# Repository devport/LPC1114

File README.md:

# LPC1114
LPC1114 in FreePascal

UNITS FOR:
--- ENC28J60, SH1106 OLED, OneWire, DS18B20, UART, SPI, ADC, SysTick Timer, Delay (Timers) and utility ---

Binutils:
Download http://ftp.gnu.org/gnu/binutils/binutils-2.20.tar.bz2
Unzip in binutils-2.20
Create a directory binutils-arm
From binutils-arm run: ../binutils-2.20/configure --target=arm-elf --disable-nls --prefix=directory_where_you_want_binutils_installed
Build using: make all install

or download binary for windows and copy to 'c:\cross':
https://svn.freepascal.org/svn/fpcbuild/binaries/i386-win32/

FPC:
1. Requires trunk version of FPC instal to 'c:\fpc'
2. Get source FPC -> extract to 'c:\fpc_src'
3. Copy lpc11xx.pp to fpc_src\rtl\embedded\arm and replace (my version is for LPC1114XL (2xSPI etc))
4. Go to fpc_src directory and Build using: 

PATH=C:\fpc\3.0.4\bin\i386-win32;C:\cross

make clean buildbase installbase CROSSINSTALL=1 OS_TARGET=embedded CPU_TARGET=arm SUBARCH=armv6m

* C:\fpc\3.0.4\bin\i386-win32 << directory FPC
* C:\cross  << binary files fpcBuild (arm-embedded-as, arm-embedded-ld, etc.)

5. Copy fpc_src\compiler\ppcrossarm.exe to fpc\3.0.4\bin\i386-win32
6. Copy directory fpc_src\rtl\units\arm-embedded to fpc\3.0.4\units

Compile projects using:

ppcrossarm  -Fu..\units -Sc -O1 -Cparmv6m -Parm -Tembedded -Wplpc1114FBD48_303 project.pas

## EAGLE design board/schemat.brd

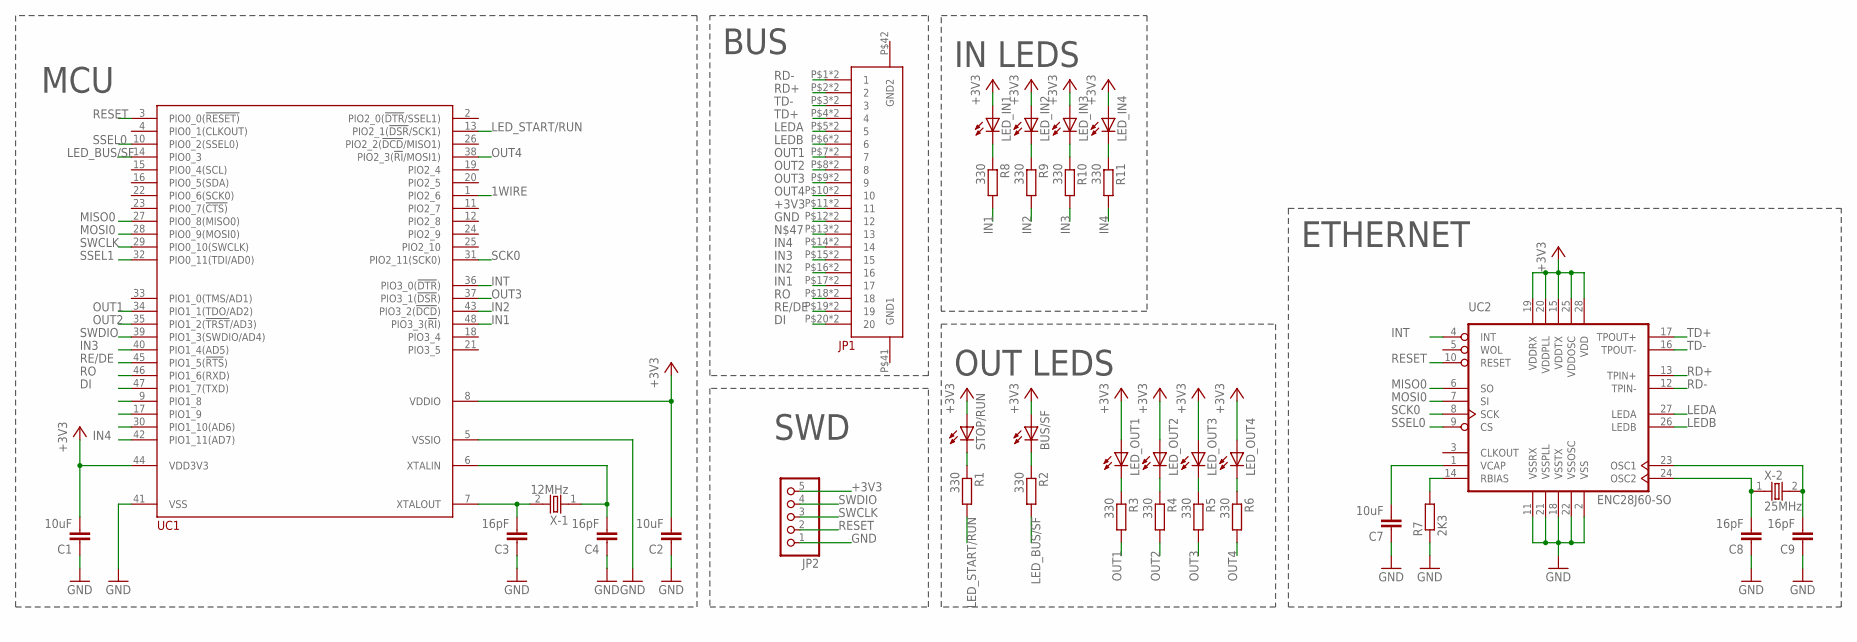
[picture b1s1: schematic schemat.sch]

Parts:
BUS/SF: LED3MM
C1, C2, C7: 10uF; C0805
C3, C4, C8, C9: 16pF; C0805
JP1: FFC(FPC)_ZIF_20_PINV; PCA-2C-20-V-3
JP2: PINHD-1X5; 1X05
LED_IN1, LED_IN2, LED_IN3, LED_IN4: LED3MM
LED_OUT1, LED_OUT2, LED_OUT3, LED_OUT4: LED3MM
R1, R2, R3, R4, R5, R6, R8, R9, R10, R11: 330; R0805W
R7: 2K3; R0805
STOP/RUN: LED3MM
UC1: NXP-LPC111X; LQFP48
UC2: ENC28J60-SO; SO28W
X-1: 12MHz; HC49UP
X-2: 25MHz; HC49UP

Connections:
1WIRE: UC1.1 (PIO2_6)
+3V3: BUS/SF.A, C1.2, C2.2, JP1.P$11 (11), JP1.P$31 (11), JP2.5, LED_IN1.A, LED_IN2.A, LED_IN3.A, LED_IN4.A, LED_OUT1.A, LED_OUT2.A, LED_OUT3.A, LED_OUT4.A, STOP/RUN.A, UC1.8 (VDDIO), UC1.44 (VDD3V3), UC2.15 (VDDTX), UC2.19 (VDDRX), UC2.20 (VDDPLL), UC2.25 (VDDOSC), UC2.28 (VDD)
DI: JP1.P$20 (20), JP1.P$40 (20), UC1.47 (PIO1_7(TXD))
GND: C1.1, C2.1, C3.1, C4.1, C7.1, C8.1, C9.1, JP1.P$12 (12), JP1.P$32 (12), JP2.1, R7.1, UC1.5 (VSSIO), UC1.41 (VSS), UC2.2 (VSS), UC2.11 (VSSRX), UC2.18 (VSSTX), UC2.21 (VSSPLL), UC2.22 (VSSOSC)
IN1: JP1.P$17 (17), JP1.P$37 (17), R8.2, UC1.48 (PIO3_3(!RI!))
IN2: JP1.P$16 (16), JP1.P$36 (16), R9.2, UC1.43 (PIO3_2(!DCD!))
IN3: JP1.P$15 (15), JP1.P$35 (15), R10.2, UC1.40 (PIO1_4(AD5))
IN4: JP1.P$14 (14), JP1.P$34 (14), R11.2, UC1.42 (PIO1_11(AD7))
INT: UC1.36 (PIO3_0(!DTR!)), UC2.4 (INT)
LEDA: JP1.P$5 (5), JP1.P$25 (5), UC2.27 (LEDA)
LEDB: JP1.P$6 (6), JP1.P$26 (6), UC2.26 (LEDB)
LED_BUS/SF: R2.2, UC1.14 (PIO0_3)
LED_START/RUN: R1.2, UC1.13 (PIO2_1(!DSR!/SCK1))
MISO0: UC1.27 (PIO0_8(MISO0)), UC2.6 (SO)
MOSI0: UC1.28 (PIO0_9(MOSI0)), UC2.7 (SI)
unnamed: C3.2, UC1.7 (XTALOUT), X-1.2
unnamed: C4.2, UC1.6 (XTALIN), X-1.1
unnamed: C8.2, UC2.24 (OSC2), X-2.1
unnamed: R1.1, STOP/RUN.K (C)
unnamed: LED_IN4.K (C), R11.1
unnamed: BUS/SF.K (C), R2.1
unnamed: LED_OUT4.K (C), R6.1
unnamed: LED_IN1.K (C), R8.1
unnamed: LED_IN2.K (C), R9.1
unnamed: LED_IN3.K (C), R10.1
unnamed: LED_OUT3.K (C), R5.1
unnamed: LED_OUT2.K (C), R4.1
unnamed: LED_OUT1.K (C), R3.1
unnamed: C9.2, UC2.23 (OSC1), X-2.2
unnamed: C7.2, UC2.1 (VCAP)
unnamed: R7.2, UC2.14 (RBIAS)
unnamed: JP1.P$13 (13), JP1.P$33 (13)
OUT1: JP1.P$7 (7), JP1.P$27 (7), R3.2, UC1.34 (PIO1_1(TDO/AD2))
OUT2: JP1.P$8 (8), JP1.P$28 (8), R4.2, UC1.35 (PIO1_2(!TRST!/AD3))
OUT3: JP1.P$9 (9), JP1.P$29 (9), R5.2, UC1.37 (PIO3_1(!DSR!))
OUT4: JP1.P$10 (10), JP1.P$30 (10), R6.2, UC1.38 (PIO2_3(!RI!/MOSI1))
RD+: JP1.P$2 (2), JP1.P$22 (2), UC2.13 (TPIN+)
RD-: JP1.P$1 (1), JP1.P$21 (1), UC2.12 (TPIN-)
RE/DE: JP1.P$19 (19), JP1.P$39 (19), UC1.45 (PIO1_5(!RTS!))
RESET: JP2.2, UC1.3 (PIO0_0(!RESET)), UC2.10 (RESET)
RO: JP1.P$18 (18), JP1.P$38 (18), UC1.46 (PIO1_6(RXD))
SCK0: UC1.31 (PIO2_11(SCK0)), UC2.8 (SCK)
SSEL0: UC1.10 (PIO0_2(SSEL0)), UC2.9 (CS)
SSEL1: UC1.32 (PIO0_11(TDI/AD0))
SWCLK: JP2.3, UC1.29 (PIO0_10(SWCLK))
SWDIO: JP2.4, UC1.39 (PIO1_3(SWDIO/AD4))
TD+: JP1.P$4 (4), JP1.P$24 (4), UC2.17 (TPOUT+)
TD-: JP1.P$3 (3), JP1.P$23 (3), UC2.16 (TPOUT-)

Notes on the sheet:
SWD
MCU
ETHERNET
OUT LEDS
IN LEDS
BUS

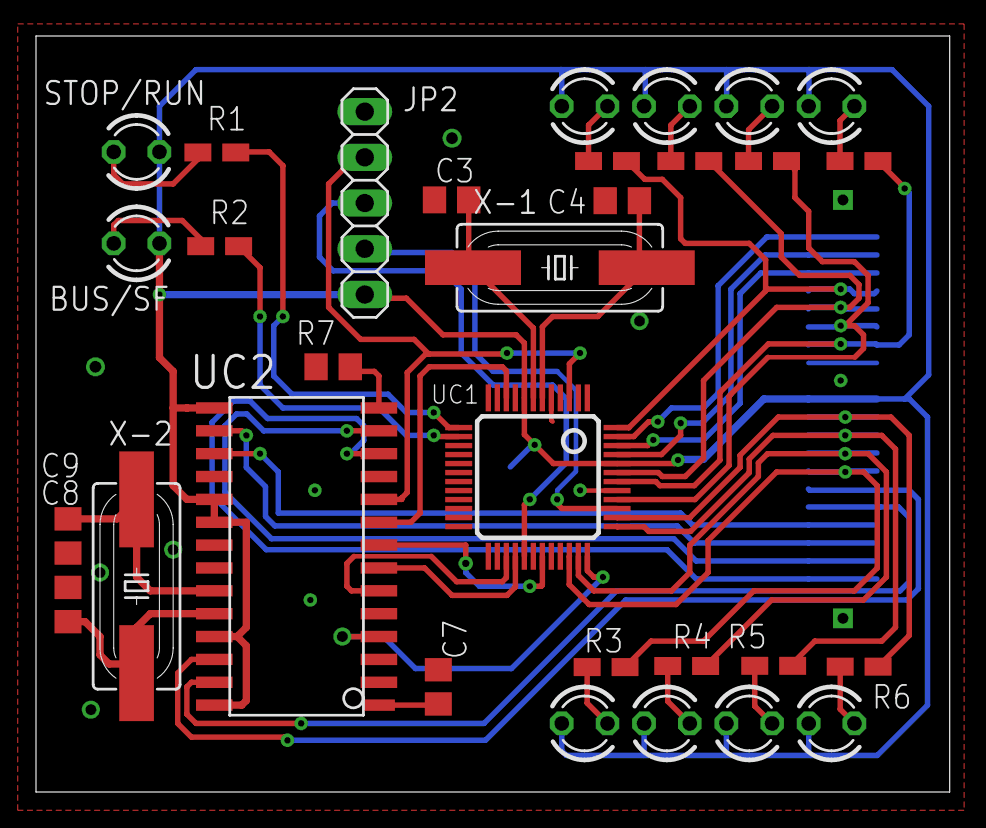
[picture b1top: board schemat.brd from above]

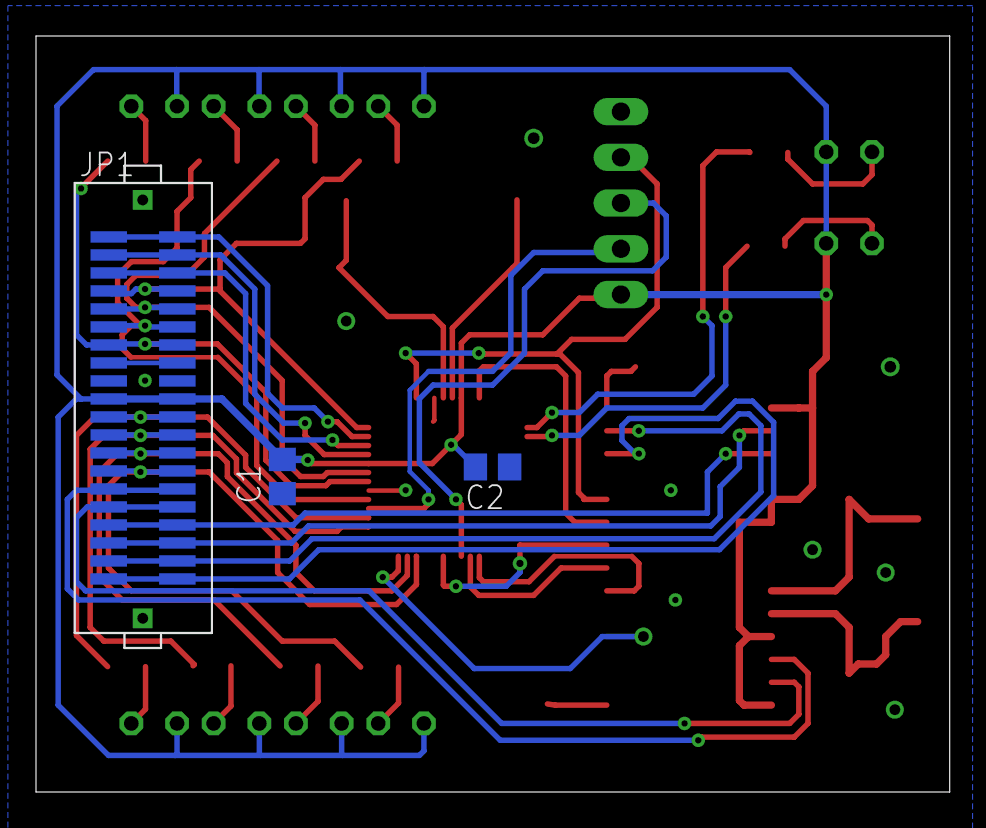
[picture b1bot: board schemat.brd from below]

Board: 2 copper layers, 50.8 x 42.0 mm, 34 parts (3 on the bottom side), 46 nets.

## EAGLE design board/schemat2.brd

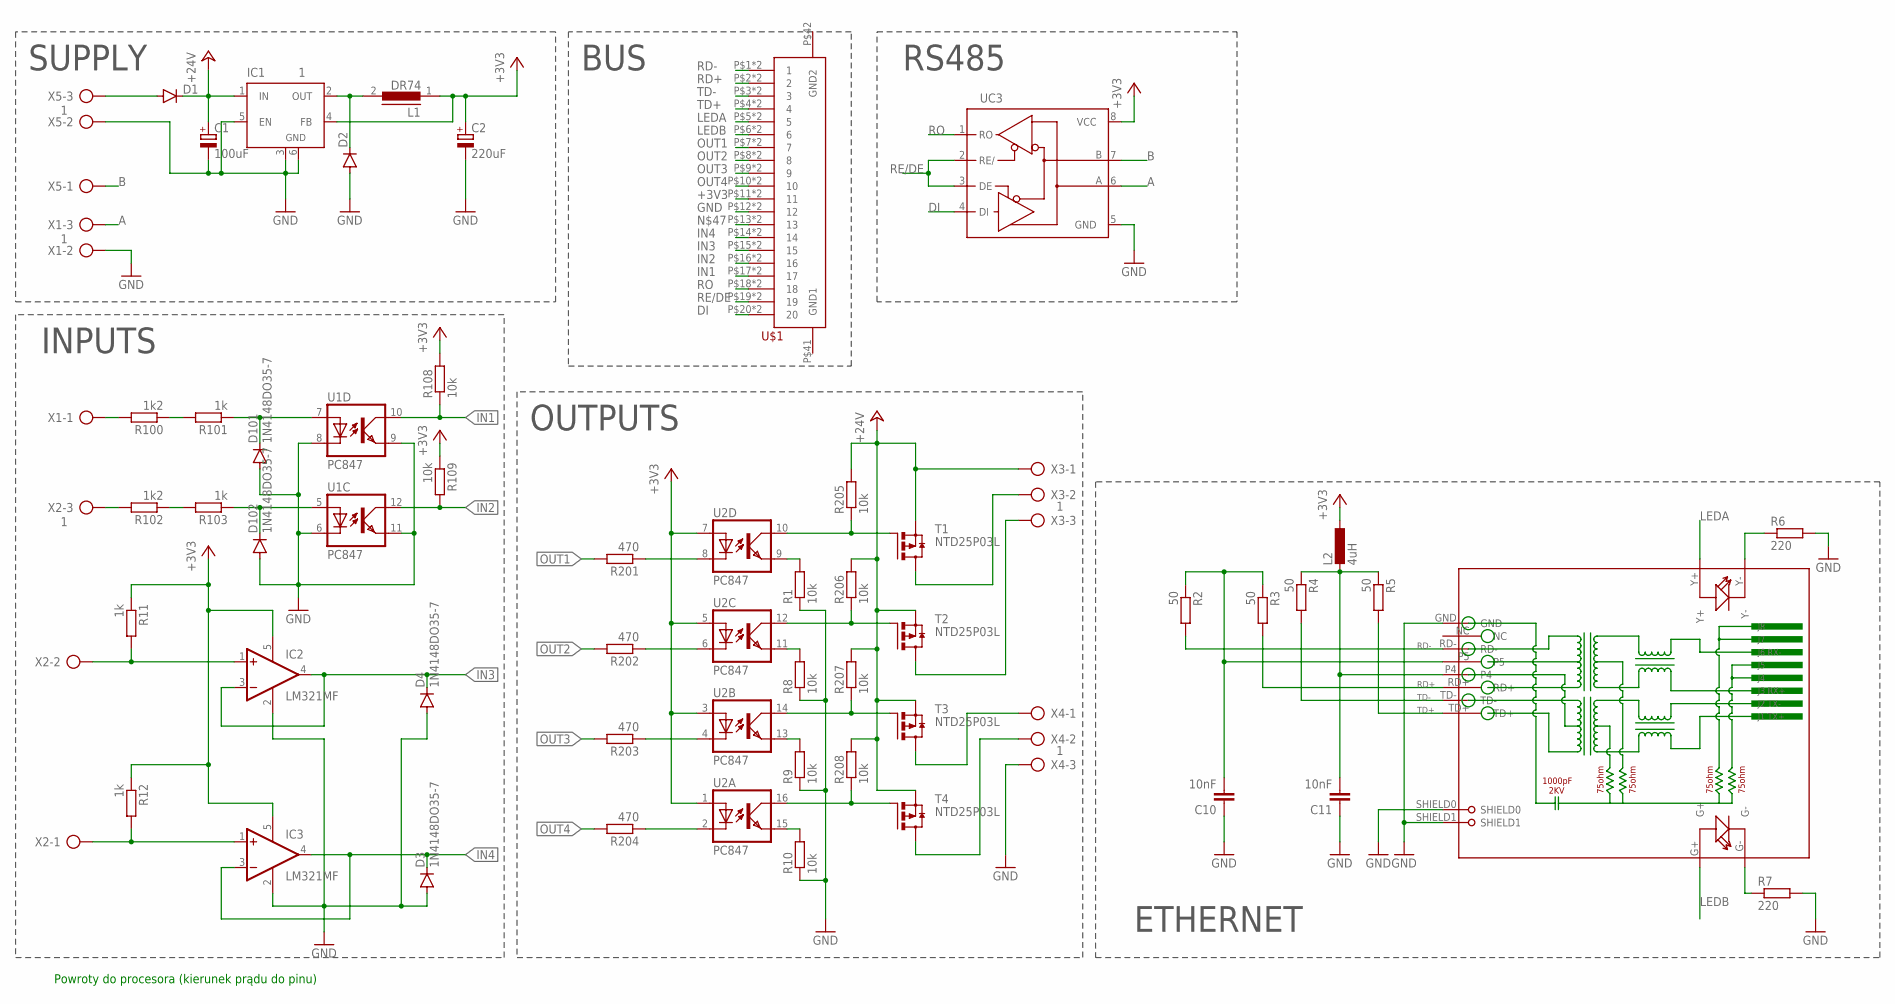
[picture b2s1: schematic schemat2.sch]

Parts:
C1: 100uF; SANYO-OSCON_SMD_E7
C2: 220uF; SANYO-OSCON_SMD_E7
C10, C11: 10nF; C0805
D1, D2: S1M; SMA
D3, D4, D101, D102: 1N4148DO35-7; DO35-7
IC1: 1; TO263-5
IC2, IC3: LM321MF; SOT23-5
L1: DR74
L2: 4uH; L2012C
R1, R8, R9, R10, R205, R206, R207, R208: 10k; R0805W
R2, R3, R4, R5: 50; R0805
R6, R7: 220; R0805
R11, R12, R101, R103: 1k; R0805
R100, R102: 1k2; R0805
R108, R109: 10k; R0805
R201, R202, R203, R204: 470; R0805
RJ1: HR911105A
T1, T2, T3, T4: NTD25P03L; DPACK
U1, U2: PC847; SO16
U$1: FFC(FPC)_ZIF_20_PINV; PCA-2C-20-V-3
UC3: MAX3468CSA; SO08
X1, X2, X3, X4, X5: 1; AK500/3

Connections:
+3V3: C2.+, IC1.4 (FB), IC2.5 (V+), IC3.5 (V+), L1.1, L2.1, R11.1, R12.1, R108.2, R109.1, U2.1 (A), U2.3 (A), U2.5 (A), U2.7 (A), U$1.P$11 (11), U$1.P$31 (11), UC3.8 (VCC)
+24V: C1.+, D1.C, IC1.1 (IN), R205.2, R206.2, R207.2, R208.2, T1.3 (S), T2.3 (S), T3.3 (S), T4.3 (S), X3.1
A: UC3.6 (A), X1.3
B: UC3.7 (B), X5.1
DI: U$1.P$20 (20), U$1.P$40 (20), UC3.4 (DI)
GND: C1.-, C2.-, C10.1, C11.1, D2.A, D3.A, D4.A, D101.A, D102.A, IC1.3 (GND), IC1.5 (EN), IC1.6 (GND), IC2.2 (V-), IC3.2 (V-), R1.1, R6.2, R7.2, R8.1, R9.1, R10.1, RJ1.GND, RJ1.SHIELD0, RJ1.SHIELD1, U1.6 (C), U1.8 (C), U1.9 (EMIT), U1.11 (EMIT), U$1.P$12 (12), U$1.P$32 (12), UC3.5 (GND), X1.2, X4.3, X5.2
IN1: R108.1, U1.10 (COL), U$1.P$17 (17), U$1.P$37 (17)
IN2: R109.2, U1.12 (COL), U$1.P$16 (16), U$1.P$36 (16)
IN3: D4.C, IC2.3 (-IN), IC2.4 (OUT), U$1.P$15 (15), U$1.P$35 (15)
IN4: D3.C, IC3.3 (-IN), IC3.4 (OUT), U$1.P$14 (14), U$1.P$34 (14)
LEDA: RJ1.Y+, U$1.P$5 (5), U$1.P$25 (5)
LEDB: RJ1.G+, U$1.P$6 (6), U$1.P$26 (6)
unnamed: R100.1, R101.2
unnamed: R100.2, X1.1
unnamed: R205.1, T1.1 (G), U2.10 (COL)
unnamed: R206.1, T2.1 (G), U2.12 (COL)
unnamed: D1.A, X5.3
unnamed: R207.1, T3.1 (G), U2.14 (COL)
unnamed: R208.1, T4.1 (G), U2.16 (COL)
unnamed: R102.2, X2.3
unnamed: IC3.1 (+IN), R12.2, X2.1
unnamed: T1.2 (D), X3.2
unnamed: T2.2 (D), X3.3
unnamed: T3.2 (D), X4.1
unnamed: T4.2 (D), X4.2
unnamed: R102.1, R103.2
unnamed: IC2.1 (+IN), R11.2, X2.2
unnamed: R201.1, U2.8 (C)
unnamed: R202.1, U2.6 (C)
unnamed: D101.C, R101.1, U1.7 (A)
unnamed: D102.C, R103.1, U1.5 (A)
unnamed: D2.C, IC1.2 (OUT), L1.2
unnamed: R203.1, U2.4 (C)
unnamed: R204.1, U2.2 (C)
unnamed: R1.2, U2.9 (EMIT)
unnamed: R8.2, U2.11 (EMIT)
unnamed: R9.2, U2.13 (EMIT)
unnamed: R10.2, U2.15 (EMIT)
unnamed: C10.2, R2.1, R3.1, RJ1.P5
unnamed: C11.2, L2.2, R4.1, R5.1, RJ1.P4
unnamed: R6.1, RJ1.Y-
unnamed: R7.1, RJ1.G-
unnamed: U$1.P$13 (13), U$1.P$33 (13)
OUT1: R201.2, U$1.P$7 (7), U$1.P$27 (7)
OUT2: R202.2, U$1.P$8 (8), U$1.P$28 (8)
OUT3: R203.2, U$1.P$9 (9), U$1.P$29 (9)
OUT4: R204.2, U$1.P$10 (10), U$1.P$30 (10)
RD+: R3.2, RJ1.RD+, U$1.P$2 (2), U$1.P$22 (2)
RD-: R2.2, RJ1.RD-, U$1.P$1 (1), U$1.P$21 (1)
RE/DE: U$1.P$19 (19), U$1.P$39 (19), UC3.2 (RE/), UC3.3 (DE)
RO: U$1.P$18 (18), U$1.P$38 (18), UC3.1 (RO)
TD+: R5.2, RJ1.TD+, U$1.P$4 (4), U$1.P$24 (4)
TD-: R4.2, RJ1.TD-, U$1.P$3 (3), U$1.P$23 (3)

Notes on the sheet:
SUPPLY
ETHERNET
Powroty do procesora (kierunek prądu do pinu)
RS485
BUS
INPUTS
OUTPUTS

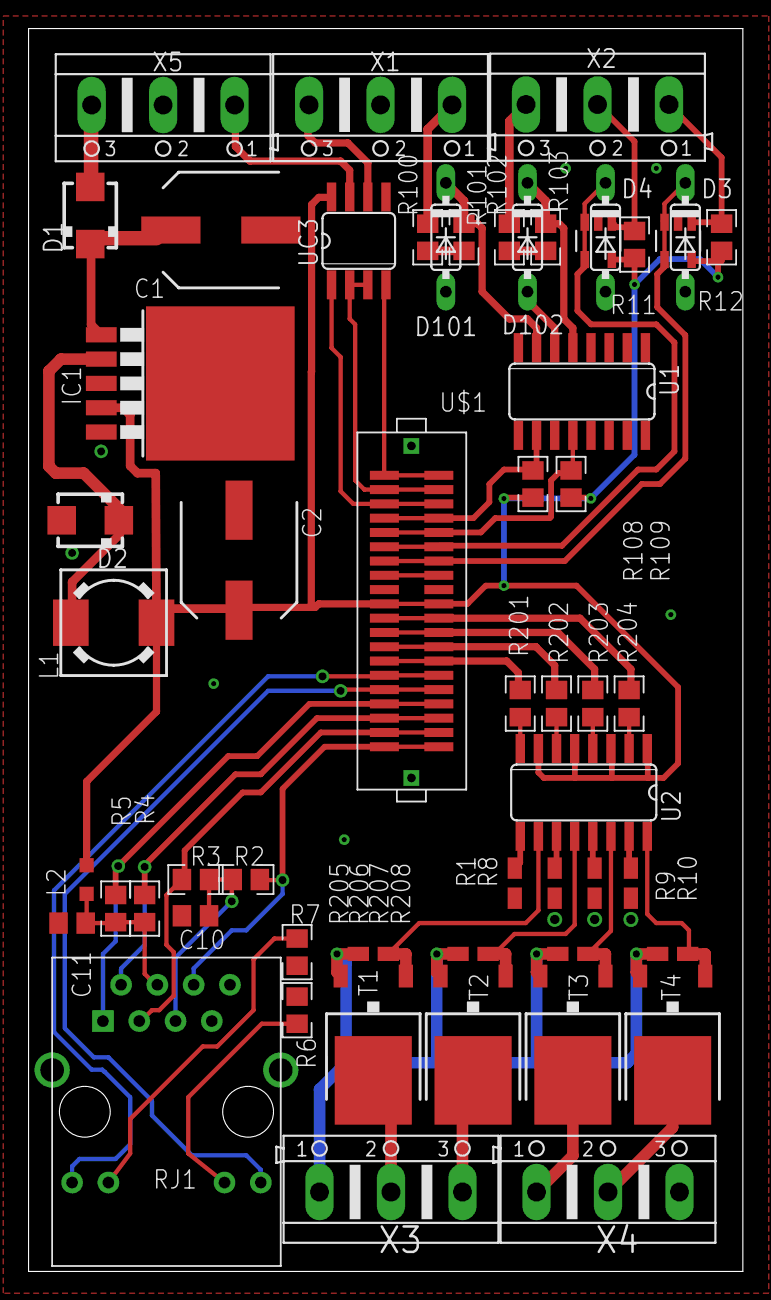
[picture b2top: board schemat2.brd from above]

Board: 2 copper layers, 50.0 x 87.0 mm, 55 parts (0 on the bottom side), 53 nets.

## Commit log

2019-11-27 OLED + DS18B20
    Test OLED SH1106 and temperature Sensor DS18B20 (one wire)
2019-11-27 Rename Project.pas to Project1.pas
2019-11-27 Rename project2.lpr to Project2.pas
2019-11-27 Update to UM10398 Rev. 11
    +MASKED_ACCESS in TGPIO_Registers range 0..4094
    +DATA in TGPIO_Registers
    +SSEL1_LOC replace RESERVED1 in TIOCON_Registers
    - FIFOLVL from TUART_Registers
2019-11-30 SysTick Timer Demo
2019-11-30 Add definition for SysTick Timer
2019-11-30 change to -MObjfpc
2019-12-06 add simple udp support
2019-12-15 add simple stack TCP/IP
2020-01-01 Cosmetic changes
2020-01-01 Web Driver for Domoticz
2020-01-01 Board in Eagle
2020-01-08 add my simple IL implementation
    Compiler and interpreter.
    Include command:
    - LD, ST, = (load, store, assign)
    - A (And), AN, (NAND), O (OR), NO
    - SET, CLR (Set accumulator or Clear)
    Example:
2020-01-08 add my IL implementation
2020-01-11 optimizations
2020-01-12 Add UDP support
2020-01-12 Add UDP Support & update
2020-01-12 UDP support
